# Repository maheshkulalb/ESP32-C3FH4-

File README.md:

# ESP32-C3FH4 Development Board (External Antenna)

## Overview
This repository contains the complete open-source hardware design for a custom development board based on the Espressif **ESP32-C3FH4** SoC (RISC-V 32-bit single-core, integrated 4MB Flash). 

Unlike standard modules that rely on a PCB trace antenna, this design specifically routes the RF path to an external antenna connector , making it ideal for deployments inside metal enclosures or applications requiring higher-gain antennas. 

## Key Features
* **Microcontroller:** ESP32-C3FH4 (RISC-V 32-bit, 160MHz, built-in 4MB Flash)
* **Connectivity:** 2.4 GHz Wi-Fi and Bluetooth 5 (LE)
* **RF Interface:** connector with impedance-matched 50Ω RF routing
* **USB Interface:** USB Type-C for power and direct Serial flashing
* **Power Supply:** 5V to 3.3V LDO regulator 
* **I/O Breakout:** Standard 2.54mm pitch headers 
* **User Interface:** Reset button, User Boot button (GPIO9)

## EDA Tool & Source Files
This project is designed entirely in **KiCad** 

The native KiCad project files are included, allowing you to modify the schematics, tweak the PCB layout, or export custom manufacturing files.

### Repository Structure
* `/Hardware` - Native KiCad project files (`.kicad_pro`, `.kicad_sch`, `.kicad_pcb`)
* `/Gerbers` - Ready-to-manufacture Gerber and Drill files

**Recommended Fabrication Specs:**
* **Layers:4**
* **Thickness:1.57mm**
* **Impedance Control:Yes**

You are free to use, modify, and distribute this design

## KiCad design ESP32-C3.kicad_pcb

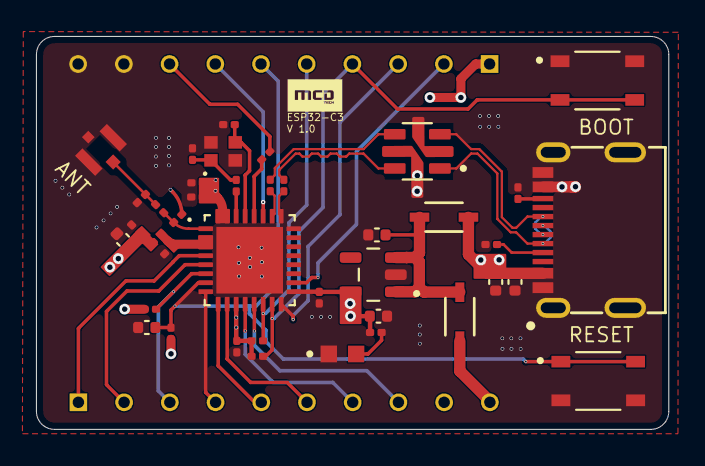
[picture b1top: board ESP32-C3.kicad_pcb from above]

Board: 4 copper layers, 35.1 x 21.8 mm, 42 parts (0 on the bottom side), 36 nets.

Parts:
C1: 1.8pF 6.3V; C_0201_0603Metric
C2: 1.2pF 6.3V; C_0201_0603Metric
C3, C9: 1uF 6.3V; C_0201_0603Metric
C4, C6, C7: 0.1uF 6.3V; C_0201_0603Metric
C5: 10uF 6.3V; C_0402_1005Metric
C8: 10nF 6.3V; C_0201_0603Metric
C10: 1uF 10V; C_0402_1005Metric
C11, C14: 1uF 6.3V; C_0402_1005Metric
C12, C13: 9.8pF 6.3V; C_0201_0603Metric
C18: 10uF 10V; C_0402_1005Metric
C19: 0.1uF 10V; C_0402_1005Metric
D1: LTST-C191KFKT; LEDC1608X55N
D2, D3: NSR0320MW2T3G; SOD-323_1P8X1P35_ONS-M
J1: USB4215-03-A; CONN_8p94X6p5X3p16_12L_GCC
J3, J4: TS-110-T-AA; SAMTEC_TS-110-T-AA
J5: CONMHF4-SMD-G-T; TE_CONMHF4-SMD-G-T
L1: 3nH; L_0201_0603Metric
L2: 2nH; L_0201_0603Metric
R1: 499R; R_0201_0603Metric
R2: 130R; R_0201_0603Metric
R4: 0R; C_0201_0603Metric
R5, R6, R7, R8: 10K; R_0201_0603Metric
R10, R11: 22R; R_0201_0603Metric
R13, R14: 5.1K 1%; R_0201_0603Metric
S1, S2: SKRPABE010; SW_SKRPABE010
U1: ESP32-C3FH4; QFN50P500X500X90-33N
U2: USBLC6-2SC6; SOT95P280X145-6N
U3: TLV75733PDBVR; SOT95P280X145-5N
Y1: XRCGB40M000F1S1LR0; OSC_XRCGB40M000F1S1AR0

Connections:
+3V3: C4.1, C5.1, C6.1, C7.1, C8.1, C9.1, C11.1, J3.09, J4.01, L2.2, R2.2, R5.2, R6.2, R7.1, R8.1, U1.11 (VDD3P3_RTC), U1.17 (VDD3P3_CPU), U1.31 (VDDA), U1.32 (VDDA__1), U3.5 (OUT)
+5V: C18.1, C19.1, D2.2 (A), J1.A4/B9 (VBUS), J1.B4/A9 (VBUS), U2.5
/ESP32_C3/0.635 trace: C3.1, L2.1, U1.2 (VDD3P3), U1.3 (VDD3P3__1)
/ESP32_C3/ANT: C2.1, J5.1, L1.2
/ESP32_C3/D0_N: R10.1, U1.25 (GPIO18/USB_D-)
/ESP32_C3/D0_P: R11.1, U1.26 (GPIO19/USB_D+)
/ESP32_C3/D_N: R10.2, U2.6
/ESP32_C3/D_P: R11.2, U2.4
/ESP32_C3/GPIO0: J3.01, U1.4 (GPIO0/XTAL_32K_P)
/ESP32_C3/GPIO1: J3.02, U1.5 (GPIO1/XTAL_32K_N)
/ESP32_C3/GPIO2: J3.03, R7.2, U1.6 (GPIO2)
/ESP32_C3/GPIO3: J3.04, U1.8 (GPIO3)
/ESP32_C3/GPIO4: J3.05, U1.9 (GPIO4/MTMS)
/ESP32_C3/GPIO5: J3.06, U1.10 (GPIO5/MTDI)
/ESP32_C3/GPIO6: J3.07, U1.12 (GPIO6/MTCK)
/ESP32_C3/GPIO7: J3.08, U1.13 (GPIO7/MTDO)
/ESP32_C3/GPIO8: J4.05, R6.1, U1.14 (GPIO8)
/ESP32_C3/GPIO9: J4.04, R5.1, S2.3, S2.4, U1.15 (GPIO9)
/ESP32_C3/GPIO10: J4.03, U1.16 (GPIO10)
/ESP32_C3/GPIO11: J4.02, U1.18 (VDD_SPI/GPIO)
/ESP32_C3/LNA_IN: C1.1, L1.1, U1.1 (LNA_IN)
/ESP32_C3/RST: C14.1, J4.06, R8.2, S1.1, S1.2, U1.7 (CHIP_EN)
/ESP32_C3/U0RXD: J4.07, U1.27 (GPIO20/U0RXD)
/ESP32_C3/U0TXD: J4.08, R1.2
/GPIO/VIN_5V: D3.2 (A), J3.10
/USB/DIN_N: J1.A7 (DN1), J1.B7 (DN2), U2.1
/USB/DIN_P: J1.A6 (DP1), J1.B6 (DP2), U2.3
/USB/VIN: C10.1, D2.1 (K), D3.1 (K), U3.1 (IN), U3.3 (EN)
GND: C1.2, C2.2, C3.2, C4.2, C5.2, C6.2, C7.2, C8.2, C9.2, C10.2, C11.2, C12.2, C13.2, C14.2, C18.2, C19.2, D1.C, J1.A1/B12 (GND), J1.B1/A12 (GND), J1.SH (GND), J4.09, J4.10, J5.2, J5.3, J5.4, R13.2, R14.2, S1.3, S1.4, S2.1, S2.2, U1.33 (GND), U2.2, U3.2 (GND), Y1.2, Y1.4
unnamed: C12.1, R4.1, Y1.1
unnamed: D1.A, R2.1
unnamed: J1.A5 (CC1), R13.1
unnamed: J1.B5 (CC2), R14.1
unnamed: R1.1, U1.28 (GPIO21/U0TXD)
unnamed: C13.1, U1.29 (XTAL_N), Y1.3
unnamed: R4.2, U1.30 (XTAL_P)

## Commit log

2026-04-23 READ.gitkeep
